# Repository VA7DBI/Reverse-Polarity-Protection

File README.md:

# Reverse-Polarity-Protection
Protection from accidental incorrect polarity. 

### Images

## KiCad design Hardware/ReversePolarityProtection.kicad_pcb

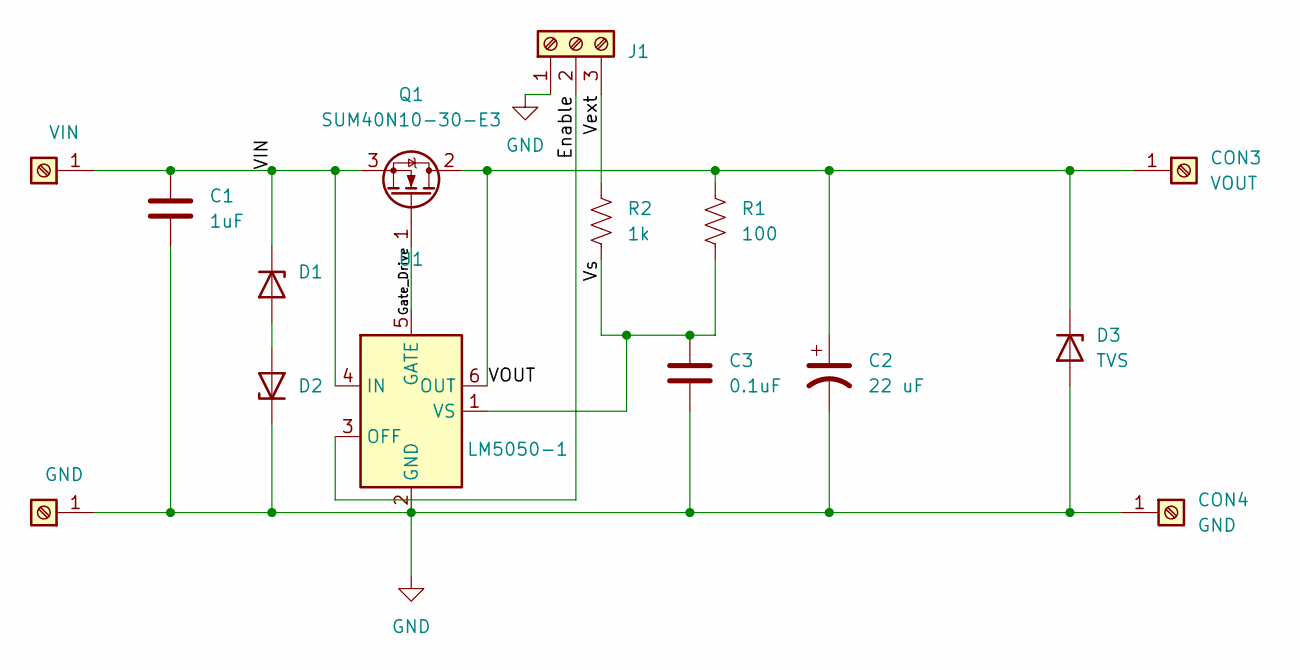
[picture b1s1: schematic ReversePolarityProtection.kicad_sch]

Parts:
C1: 1uF; C_1825_4564Metric_Pad1.57x6.80mm_HandSolder; Voltage 100V
C2: 22 uF; C_Elec_10x10.2
C3: 0.1uF; C_0805_2012Metric_Pad1.18x1.45mm_HandSolder
CON1: VIN; keystone_7808
CON2, CON4: GND; keystone_7808
CON3: VOUT; keystone_7808
D1, D2: SS16T3G; D_SMA-SMB_Universal_Handsoldering
D3: TVS; D_SMA-SMB_Universal_Handsoldering
J1: Screw_Terminal_01x02; PinHeader_1x03_P1.00mm_Vertical
Q1: SUM40N10-30-E3; TO-263-2
R1: 100; R_0603_1608Metric_Pad0.98x0.95mm_HandSolder
R2: 1k; R_0603_1608Metric_Pad0.98x0.95mm_HandSolder
U1: LM5050-1; TSOT-23-6

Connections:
/Enable: J1.2, U1.3 (OFF)
/Gate_Drive: Q1.1 (G), U1.5 (GATE)
/VIN: C1.2, CON1.1, D1.1 (K), Q1.3 (S), U1.4 (IN)
/VOUT: C2.1, CON3.1, D3.1 (K), Q1.2 (D), R1.1, U1.6 (OUT)
/Vext: J1.3, R2.1
/Vs: C3.1, R1.2, R2.2, U1.1 (VS)
GND: C1.1, C2.2, C3.2, CON2.1, CON4.1, D2.1 (K), D3.2 (A), J1.1, U1.2 (GND)
unnamed: D1.2 (A), D2.2 (A)

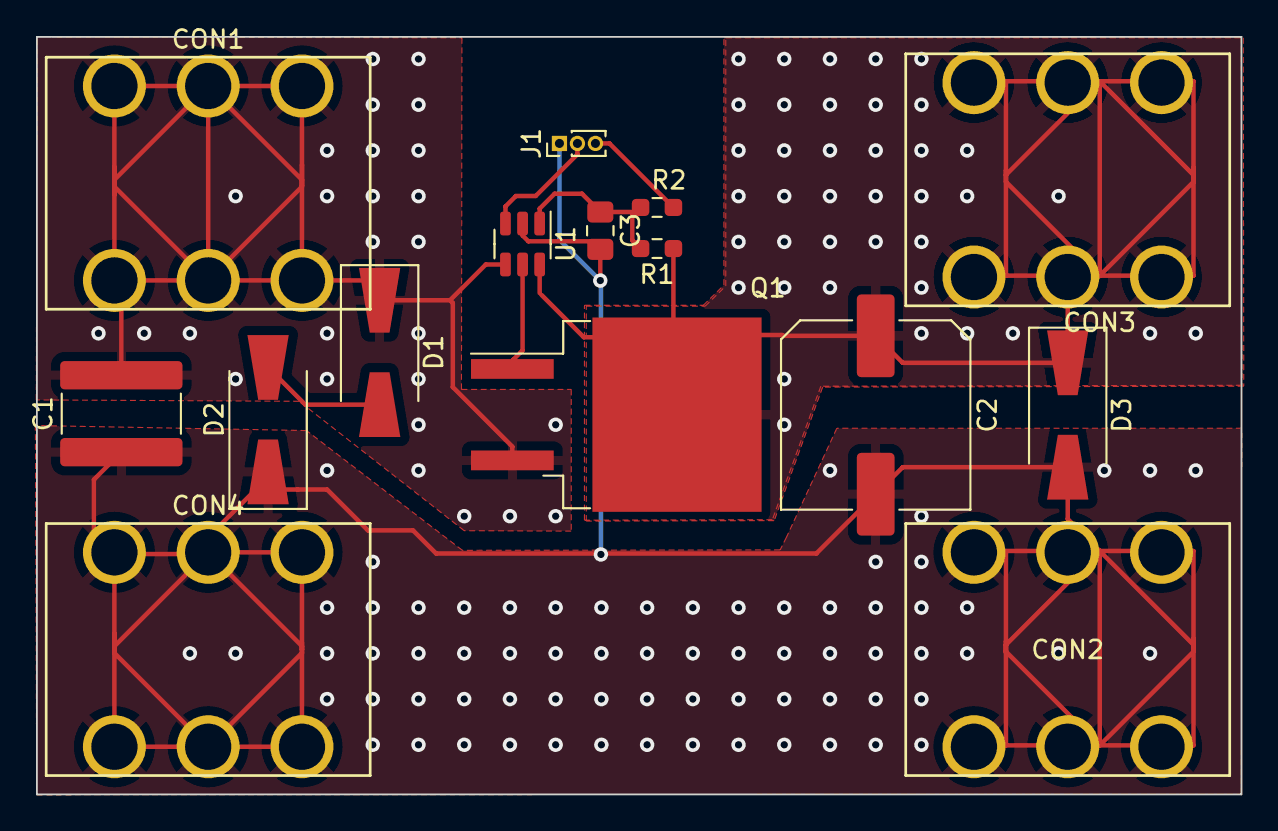
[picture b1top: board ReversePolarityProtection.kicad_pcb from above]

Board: 2 copper layers, 66.9 x 42.1 mm, 15 parts (0 on the bottom side), 8 nets.

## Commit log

2021-10-16 Initial Checkin of the project
2023-11-04 Create kicad action
    Action Workflow to automatically build & publish kicad projects
2023-11-04 Create Makefile
2023-11-04 Fix typo in Reverse-Polarity-Protection
2023-11-04 Update Makefile
2024-03-26 Create 3d renders with every PCB
    See https://github.com/linalinn/kicad-render
2024-03-26 Upgrade to kicad 8
2024-03-26 KiCad 8.0
2024-03-26 Remove spaces in Filename
2024-03-26 Generate Fabircation files
2024-05-23 fix URL for workflow
2024-05-23 Fix missing D2
2024-05-23 update CI
2024-05-23 Update jlpcb.yml to use actions v4
